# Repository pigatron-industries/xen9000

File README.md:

# XEN-9000
This project documents a completely DIY modular synthesizer build.

## Contents

* [Build Process](build_process.md)
* [Modules](modules/modules.md)

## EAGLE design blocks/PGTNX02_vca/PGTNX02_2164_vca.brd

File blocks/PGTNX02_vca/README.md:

# History

PGTNX02_2164

## V1
* Unlabelled
* C15 has wrong polarity.
* Linear/Exponential switch headers are mislabelled and inner ones are in the wrong order.
  SWLxx should be SWCxx. SWCxx should be SWExx. SWExx should be SWLxx.

Connections for Exponential mode:

```
  * *
    |
  * *
  |
  * *
```

Connections for Linear mode:

```
  * *--+
  |    |
  * *  |
       |
  * *--+
```

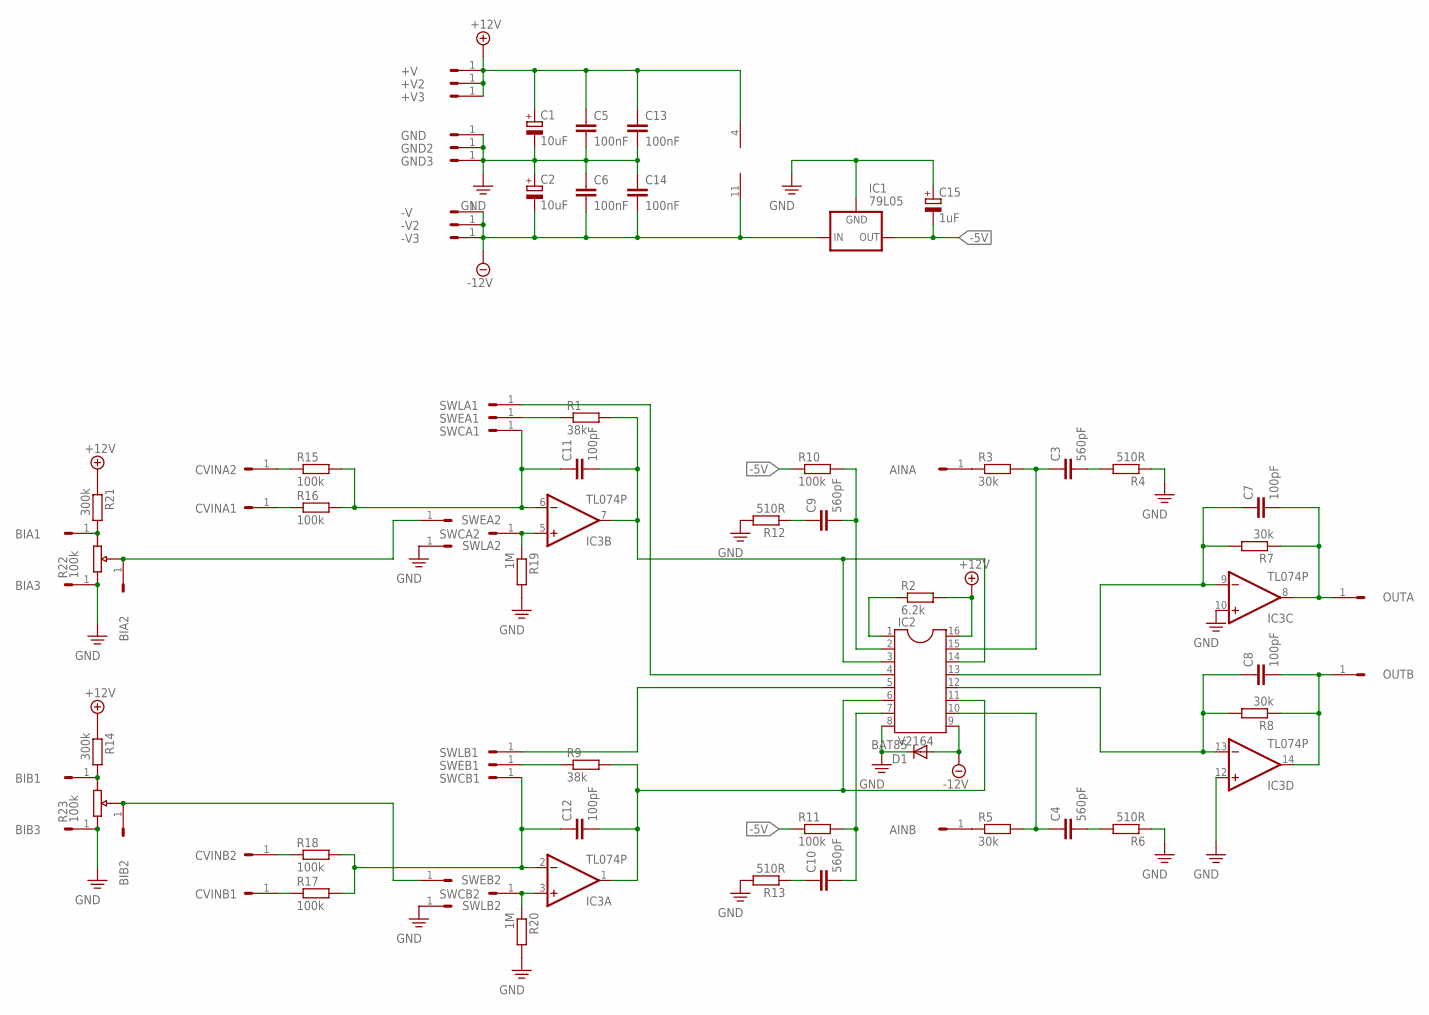
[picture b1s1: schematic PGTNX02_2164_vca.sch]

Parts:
+V, +V2, +V3: HEADER/MALE/01
-V, -V2, -V3: HEADER/MALE/01
AINA: HEADER/MALE/01
AINB: HEADER/MALE/01
BIA1, BIA2, BIA3: HEADER/MALE/01
BIB1, BIB2, BIB3: HEADER/MALE/01
C1, C2: 10uF; E2,5-6
C3, C4, C9, C10: 560pF; CERAMICDISC/5
C5, C6, C13, C14: 100nF; CERAMICDISC/5
C7, C8, C11, C12: 100pF; CERAMICDISC/5
C15: 1uF; E2,5-6
CVINA1, CVINA2: HEADER/MALE/01
CVINB1, CVINB2: HEADER/MALE/01
D1: BAT85; DO35-7
GND, GND2, GND3: HEADER/MALE/01
IC1: 79L05; 79LXX
IC2: V2164; DIL16
IC3: TL074P; DIL14
OUTA: HEADER/MALE/01
OUTB: HEADER/MALE/01
R1, R9: 38k; RESISTOR/7.5
R2: 6.2k; RESISTOR/7.5
R3, R5, R7, R8: 30k; RESISTOR/7.5
R4, R6, R12, R13: 510R; RESISTOR/7.5
R10, R11, R15, R16, R17, R18: 100k; RESISTOR/7.5
R14, R21: 300k; RESISTOR/7.5
R19, R20: 1M; RESISTOR/7.5
SWCA1, SWCA2: HEADER/MALE/01
SWCB1, SWCB2: HEADER/MALE/01
SWEA1, SWEA2: HEADER/MALE/01
SWEB1, SWEB2: HEADER/MALE/01
SWLA1, SWLA2: HEADER/MALE/01
SWLB1, SWLB2: HEADER/MALE/01

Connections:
+12V: +V.1, +V2.1, +V3.1, C1.+, C5.1, C13.1, IC2.16, IC3.4 (V+), R2.2, R14.1, R21.1
-5V: C15.-, IC1.OUT, R10.1, R11.1
-12V: -V.1, -V2.1, -V3.1, C2.-, C6.2, C14.2, D1.A, IC1.IN, IC2.9, IC3.11 (V-)
unnamed: C9.2, IC2.2, R10.2
unnamed: IC2.1, R2.1
unnamed: AINA.1, R3.1
unnamed: C3.1, IC2.15, R3.2
unnamed: C3.2, R4.2
unnamed: C7.1, IC2.13, IC3.9 (-IN), R7.2
unnamed: AINB.1, R5.1
unnamed: C4.1, IC2.10, R5.2
unnamed: C4.2, R6.2
unnamed: C8.1, IC2.12, IC3.13 (-IN), R8.2
unnamed: C10.2, IC2.7, R11.2
unnamed: C9.1, R12.1
unnamed: C8.2, IC3.14 (OUT), OUTB.1, R8.1
unnamed: C7.2, IC3.8 (OUT), OUTA.1, R7.1
unnamed: R1.1, SWEA1.1
unnamed: C11.1, IC3.6 (-IN), R15.2, R16.2, SWCA1.1
unnamed: C10.1, R13.1
unnamed: C12.2, IC2.6, IC2.11, IC3.1 (OUT), R9.2
unnamed: IC2.4, SWLA1.1
unnamed: C11.2, IC2.3, IC2.14, IC3.7 (OUT), R1.2
unnamed: BIB2.1, SWEB2.1
unnamed: CVINA2.1, R15.1
unnamed: CVINA1.1, R16.1
unnamed: CVINB1.1, R17.1
unnamed: CVINB2.1, R18.1
unnamed: C12.1, IC3.2 (-IN), R17.2, R18.2, SWCB1.1
unnamed: R9.1, SWEB1.1
unnamed: IC2.5, SWLB1.1
unnamed: IC3.5 (+IN), R19.1, SWCA2.1
unnamed: IC3.3 (+IN), R20.1, SWCB2.1
unnamed: BIA1.1, R21.2
unnamed: BIB1.1, R14.2
unnamed: BIA2.1, SWEA2.1
PE: BIA3.1, BIB3.1, C1.-, C2.+, C5.2, C6.1, C13.2, C14.1, C15.+, D1.C, GND.1, GND2.1, GND3.1, IC1.GND, IC2.8, IC3.10 (+IN), IC3.12 (+IN), R4.1, R6.1, R12.2, R13.2, R19.2, R20.2, SWLA2.1, SWLB2.1

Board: 2 copper layers, 80 parts (0 on the bottom side), 37 nets, no tracks yet.

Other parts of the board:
U$1, U$2, U$3, U$4: STANDOFF/3.0
U$5: PIGATRON-LOGO

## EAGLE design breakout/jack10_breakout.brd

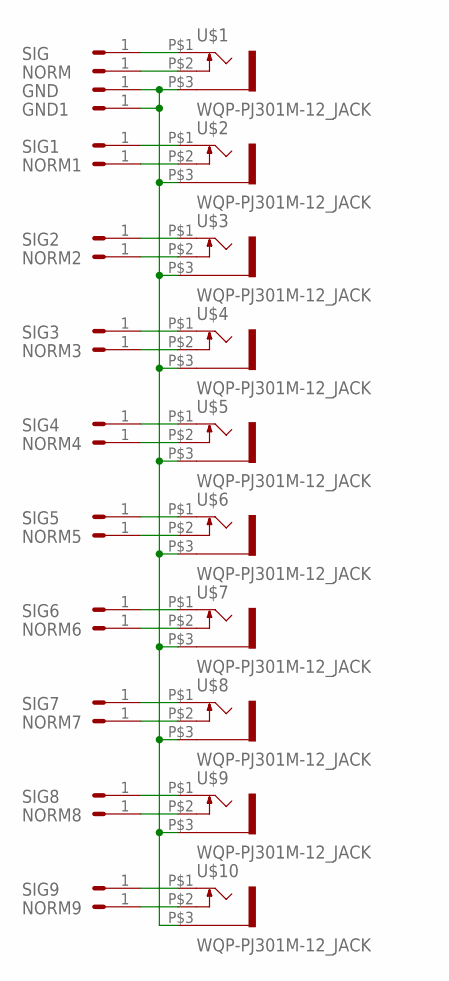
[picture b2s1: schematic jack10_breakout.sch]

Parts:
GND, GND1: HEADER/MALE/01
NORM, NORM1, NORM2, NORM3, NORM4, NORM5, NORM6, NORM7, NORM8, NORM9: HEADER/MALE/01
SIG, SIG1, SIG2, SIG3, SIG4, SIG5, SIG6, SIG7, SIG8, SIG9: HEADER/MALE/01
U$1, U$2, U$3, U$4, U$5, U$6, U$7, U$8, U$9, U$10: WQP-PJ301M-12_JACK

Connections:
unnamed: SIG.1, U$1.P$1 (2)
unnamed: NORM.1, U$1.P$2 (3)
unnamed: SIG1.1, U$2.P$1 (2)
unnamed: NORM1.1, U$2.P$2 (3)
unnamed: SIG2.1, U$3.P$1 (2)
unnamed: NORM2.1, U$3.P$2 (3)
unnamed: SIG3.1, U$4.P$1 (2)
unnamed: NORM3.1, U$4.P$2 (3)
unnamed: GND.1, GND1.1, U$1.P$3 (1), U$2.P$3 (1), U$3.P$3 (1), U$4.P$3 (1), U$5.P$3 (1), U$6.P$3 (1), U$7.P$3 (1), U$8.P$3 (1), U$9.P$3 (1), U$10.P$3 (1)
unnamed: SIG4.1, U$5.P$1 (2)
unnamed: NORM4.1, U$5.P$2 (3)
unnamed: SIG5.1, U$6.P$1 (2)
unnamed: NORM5.1, U$6.P$2 (3)
unnamed: SIG6.1, U$7.P$1 (2)
unnamed: NORM6.1, U$7.P$2 (3)
unnamed: SIG7.1, U$8.P$1 (2)
unnamed: NORM7.1, U$8.P$2 (3)
unnamed: SIG8.1, U$9.P$1 (2)
unnamed: NORM8.1, U$9.P$2 (3)
unnamed: SIG9.1, U$10.P$1 (2)
unnamed: NORM9.1, U$10.P$2 (3)

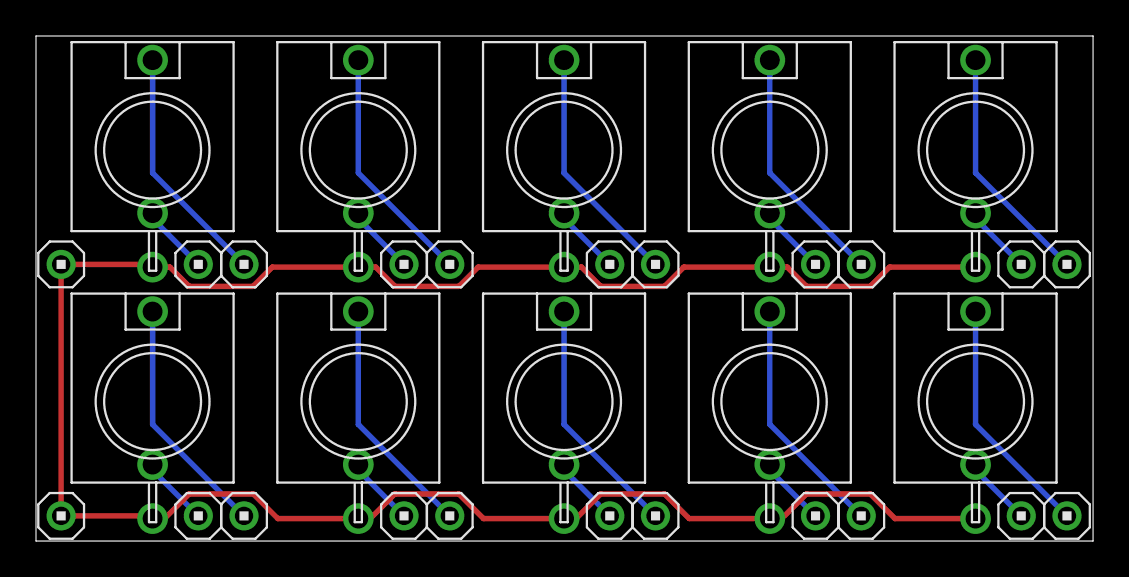
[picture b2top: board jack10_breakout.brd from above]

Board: 2 copper layers, 58.7 x 28.1 mm, 32 parts (0 on the bottom side), 21 nets.

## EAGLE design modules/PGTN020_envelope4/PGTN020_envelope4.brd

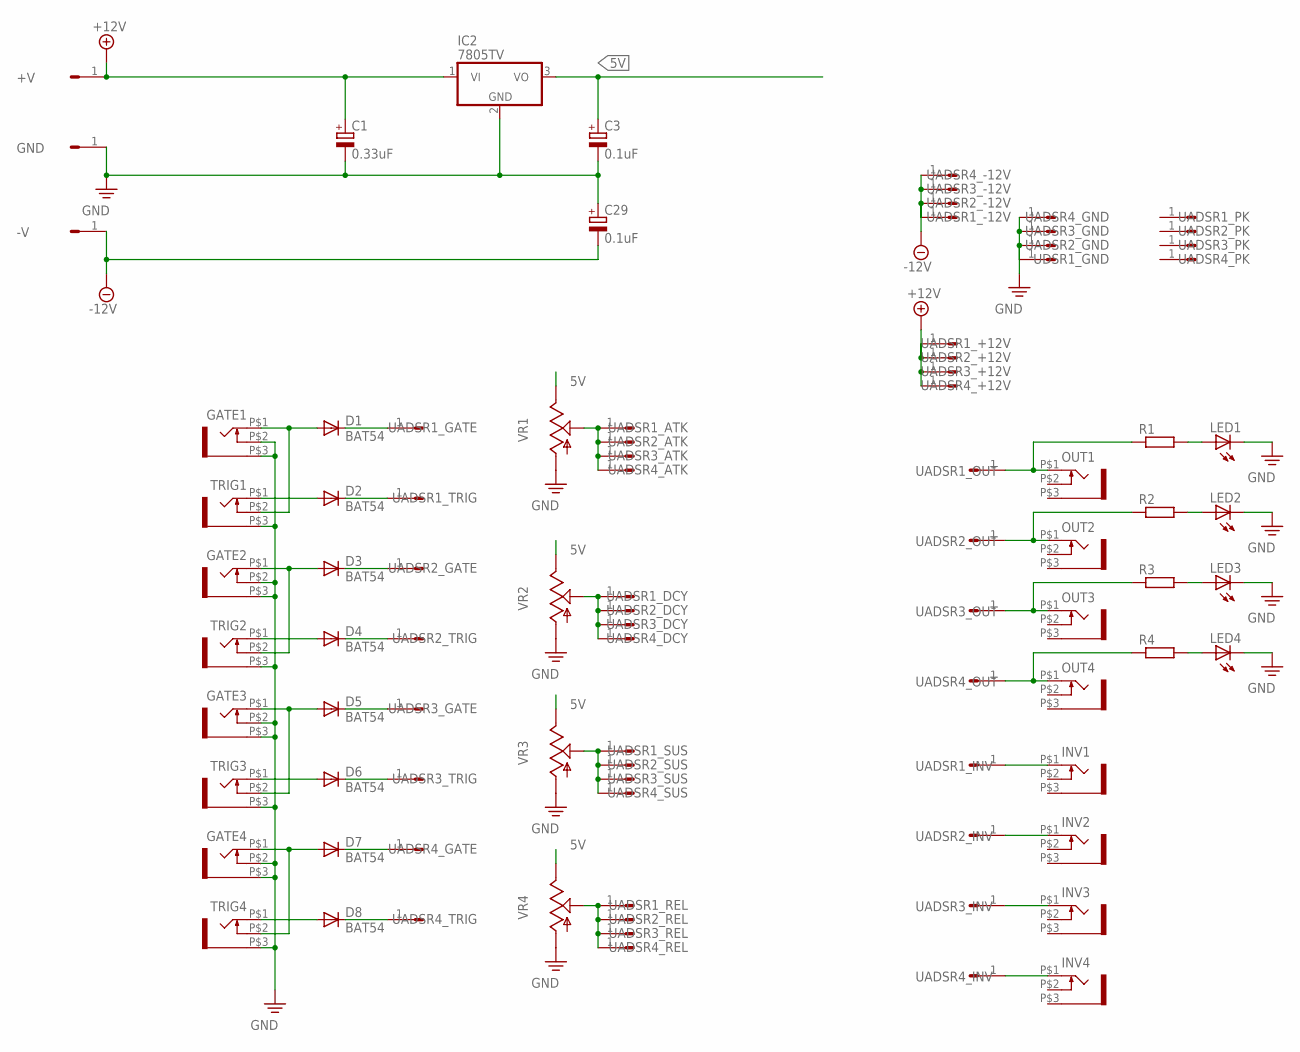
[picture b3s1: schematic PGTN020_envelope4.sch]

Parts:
+V: HEADER/MALE/01
-V: HEADER/MALE/01
C1: 0.33uF; E2,5-6
C3, C29: 0.1uF; E2,5-6
D1, D2, D3, D4, D5, D6, D7, D8: BAT54; DO35-7
GATE1, GATE2, GATE3, GATE4: WQP-PJ301M-12_JACK
GND: HEADER/MALE/01
IC2: 7805TV; TO220V
INV1, INV2, INV3, INV4: WQP-PJ301M-12_JACK
LED1, LED2, LED3, LED4: LED5MM
OUT1, OUT2, OUT3, OUT4: WQP-PJ301M-12_JACK
R1, R2, R3, R4: RESISTORRESISTOR/UPRIGHT/7.5; RESISTOR/7.5
TRIG1, TRIG2, TRIG3, TRIG4: WQP-PJ301M-12_JACK
UADSR1_+12V, UADSR1_-12V, UADSR1_ATK, UADSR1_DCY, UADSR1_GATE, UADSR1_INV, UADSR1_OUT, UADSR1_PK, UADSR1_REL, UADSR1_SUS, UADSR1_TRIG, UADSR2_+12V, UADSR2_-12V, UADSR2_ATK, UADSR2_DCY, UADSR2_GATE, UADSR2_GND, UADSR2_INV, UADSR2_OUT, UADSR2_PK, UADSR2_REL, UADSR2_SUS, UADSR2_TRIG, UADSR3_+12V, UADSR3_-12V, UADSR3_ATK, UADSR3_DCY, UADSR3_GATE, UADSR3_GND, UADSR3_INV, UADSR3_OUT, UADSR3_PK, UADSR3_REL, UADSR3_SUS, UADSR3_TRIG, UADSR4_+12V, UADSR4_-12V, UADSR4_ATK, UADSR4_DCY, UADSR4_GATE, UADSR4_GND, UADSR4_INV, UADSR4_OUT, UADSR4_PK, UADSR4_REL, UADSR4_SUS, UADSR4_TRIG: HEADER/MALE/01
UDSR1_GND: HEADER/MALE/01
VR1, VR2, VR3, VR4: 9MM_SNAP-IN_POT_; 9MM_SNAP-IN_POT

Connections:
5V: C3.+, IC2.3 (VO), VR1.3 (E), VR2.3 (E), VR3.3 (E), VR4.3 (E)
+12V: +V.1, C1.+, IC2.1 (VI), UADSR1_+12V.1, UADSR2_+12V.1, UADSR3_+12V.1, UADSR4_+12V.1
-12V: -V.1, C29.-, UADSR1_-12V.1, UADSR2_-12V.1, UADSR3_-12V.1, UADSR4_-12V.1
unnamed: OUT3.P$1 (2), R3.1, UADSR3_OUT.1
unnamed: OUT4.P$1 (2), R4.1, UADSR4_OUT.1
unnamed: INV1.P$1 (2), UADSR1_INV.1
unnamed: INV2.P$1 (2), UADSR2_INV.1
unnamed: INV3.P$1 (2), UADSR3_INV.1
unnamed: INV4.P$1 (2), UADSR4_INV.1
unnamed: D1.C, UADSR1_GATE.1
unnamed: D2.C, UADSR1_TRIG.1
unnamed: D1.A, GATE1.P$1 (2), TRIG1.P$2 (3)
unnamed: D2.A, TRIG1.P$1 (2)
unnamed: D3.A, GATE2.P$1 (2), TRIG2.P$2 (3)
unnamed: D4.A, TRIG2.P$1 (2)
unnamed: D5.A, GATE3.P$1 (2), TRIG3.P$2 (3)
unnamed: D6.A, TRIG3.P$1 (2)
unnamed: D7.A, GATE4.P$1 (2), TRIG4.P$2 (3)
unnamed: D8.A, TRIG4.P$1 (2)
unnamed: OUT1.P$1 (2), R1.1, UADSR1_OUT.1
unnamed: OUT2.P$1 (2), R2.1, UADSR2_OUT.1
unnamed: UADSR1_ATK.1, UADSR2_ATK.1, UADSR3_ATK.1, UADSR4_ATK.1, VR1.2 (S)
unnamed: UADSR1_DCY.1, UADSR2_DCY.1, UADSR3_DCY.1, UADSR4_DCY.1, VR2.2 (S)
unnamed: UADSR1_SUS.1, UADSR2_SUS.1, UADSR3_SUS.1, UADSR4_SUS.1, VR3.2 (S)
unnamed: UADSR1_REL.1, UADSR2_REL.1, UADSR3_REL.1, UADSR4_REL.1, VR4.2 (S)
unnamed: D3.C, UADSR2_GATE.1
unnamed: D4.C, UADSR2_TRIG.1
unnamed: D5.C, UADSR3_GATE.1
unnamed: D6.C, UADSR3_TRIG.1
unnamed: D7.C, UADSR4_GATE.1
unnamed: D8.C, UADSR4_TRIG.1
unnamed: LED1.A, R1.2
unnamed: LED2.A, R2.2
unnamed: LED3.A, R3.2
unnamed: LED4.A, R4.2
PE: C1.-, C3.-, C29.+, GATE1.P$2 (3), GATE1.P$3 (1), GATE2.P$2 (3), GATE2.P$3 (1), GATE3.P$2 (3), GATE3.P$3 (1), GATE4.P$2 (3), GATE4.P$3 (1), GND.1, IC2.2 (GND), LED1.K (C), LED2.K (C), LED3.K (C), LED4.K (C), TRIG1.P$3 (1), TRIG2.P$3 (1), TRIG3.P$3 (1), TRIG4.P$3 (1), UADSR2_GND.1, UADSR3_GND.1, UADSR4_GND.1, UDSR1_GND.1, VR1.1 (A), VR2.1 (A), VR3.1 (A), VR4.1 (A)

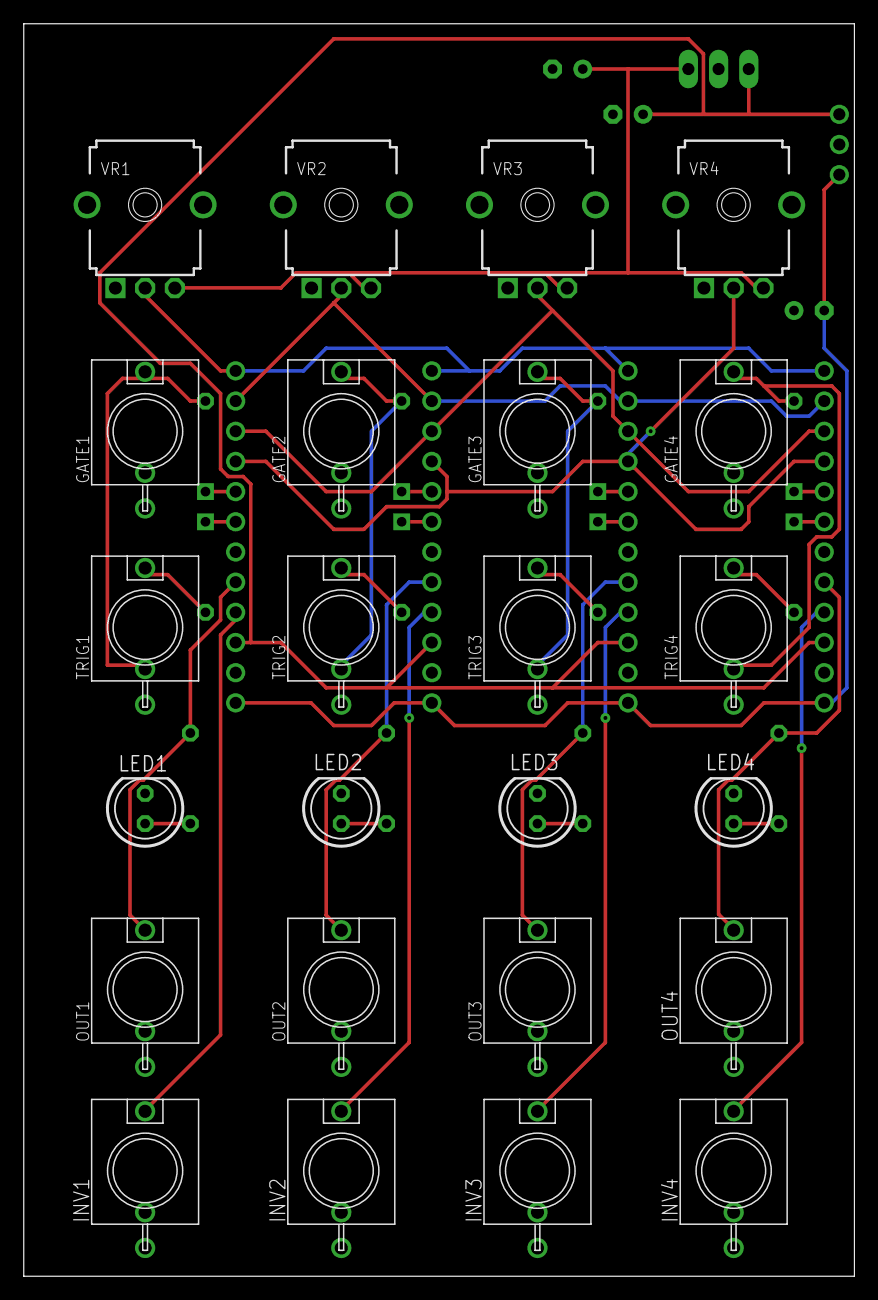
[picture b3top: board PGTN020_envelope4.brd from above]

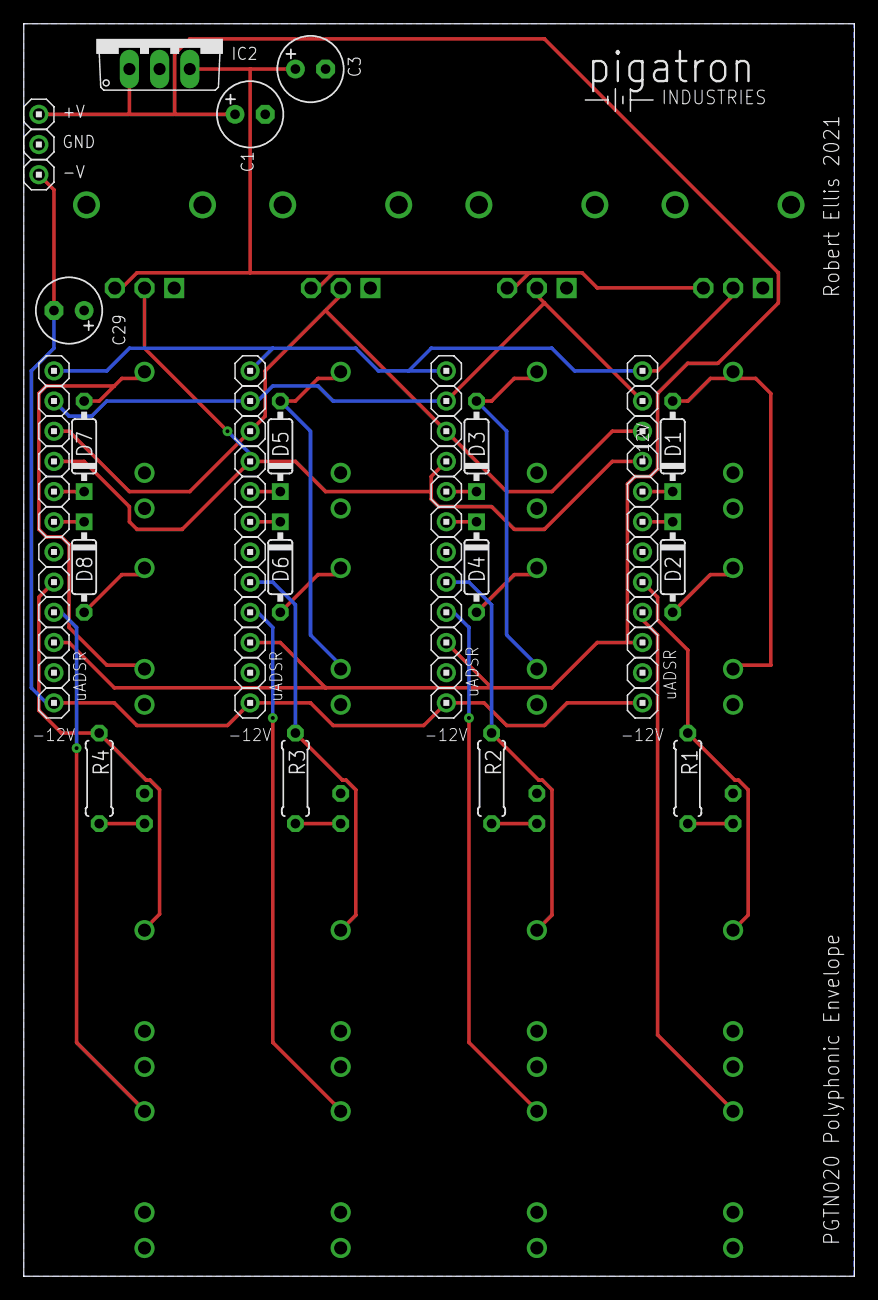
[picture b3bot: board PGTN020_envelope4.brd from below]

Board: 2 copper layers, 69.9 x 105.4 mm, 92 parts (68 on the bottom side), 36 nets.

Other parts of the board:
U$5: PIGATRON-LOGO

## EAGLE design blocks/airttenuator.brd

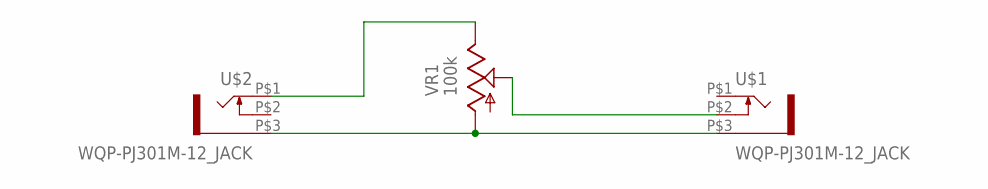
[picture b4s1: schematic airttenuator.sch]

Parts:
U$1, U$2: WQP-PJ301M-12_JACK
VR1: 100k; 9MM_SNAP-IN_POT

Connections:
unnamed: U$1.P$3 (1), U$2.P$3 (1), VR1.1 (A)
unnamed: U$2.P$1 (2), VR1.3 (E)
unnamed: U$1.P$2 (3), VR1.2 (S)

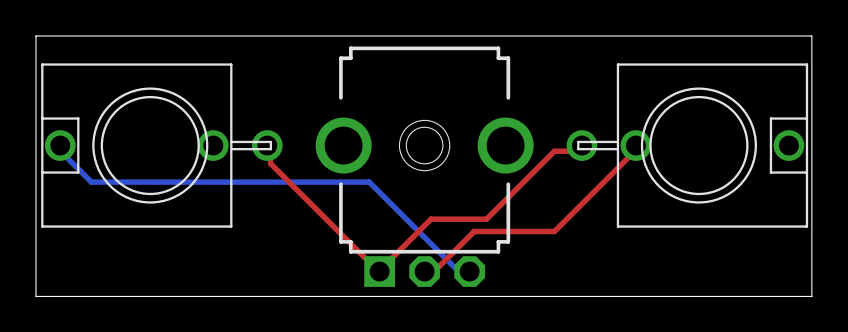
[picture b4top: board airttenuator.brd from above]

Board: 2 copper layers, 43.1 x 14.5 mm, 4 parts (1 on the bottom side), 3 nets.

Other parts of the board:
U$3: PIGATRON-LOGO

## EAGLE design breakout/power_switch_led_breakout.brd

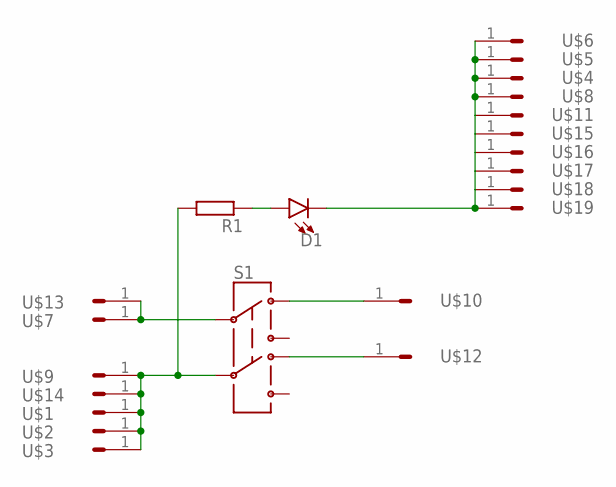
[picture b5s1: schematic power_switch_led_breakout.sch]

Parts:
D1: LED5MM; LED_5MM
R1: RESISTORRESISTOR/UPRIGHT/7.5; RESISTOR/7.5
S1: SWITCH-DPDTPTH1; SWITCH-DPDT_SUBMINIATURE
U$1, U$2, U$3, U$4, U$5, U$6, U$7, U$8, U$9, U$10, U$11, U$12, U$13, U$14, U$15, U$16, U$17, U$18, U$19: HEADER/MALE/01NOBORDER; HEADER/MALE/01/NOBORDER

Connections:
unnamed: S1.2, U$7.1, U$13.1
unnamed: S1.1, U$10.1
unnamed: D1.A, R1.1
unnamed: S1.4, U$12.1
unnamed: D1.K (C), U$4.1, U$5.1, U$6.1, U$8.1, U$11.1, U$15.1, U$16.1, U$17.1, U$18.1, U$19.1
unnamed: R1.2, S1.5, U$1.1, U$2.1, U$3.1, U$9.1, U$14.1

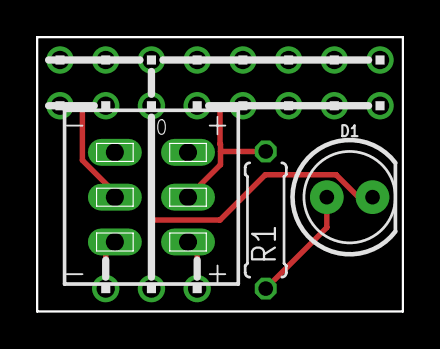
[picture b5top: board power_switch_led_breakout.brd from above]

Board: 2 copper layers, 20.3 x 15.2 mm, 22 parts (0 on the bottom side), 6 nets.

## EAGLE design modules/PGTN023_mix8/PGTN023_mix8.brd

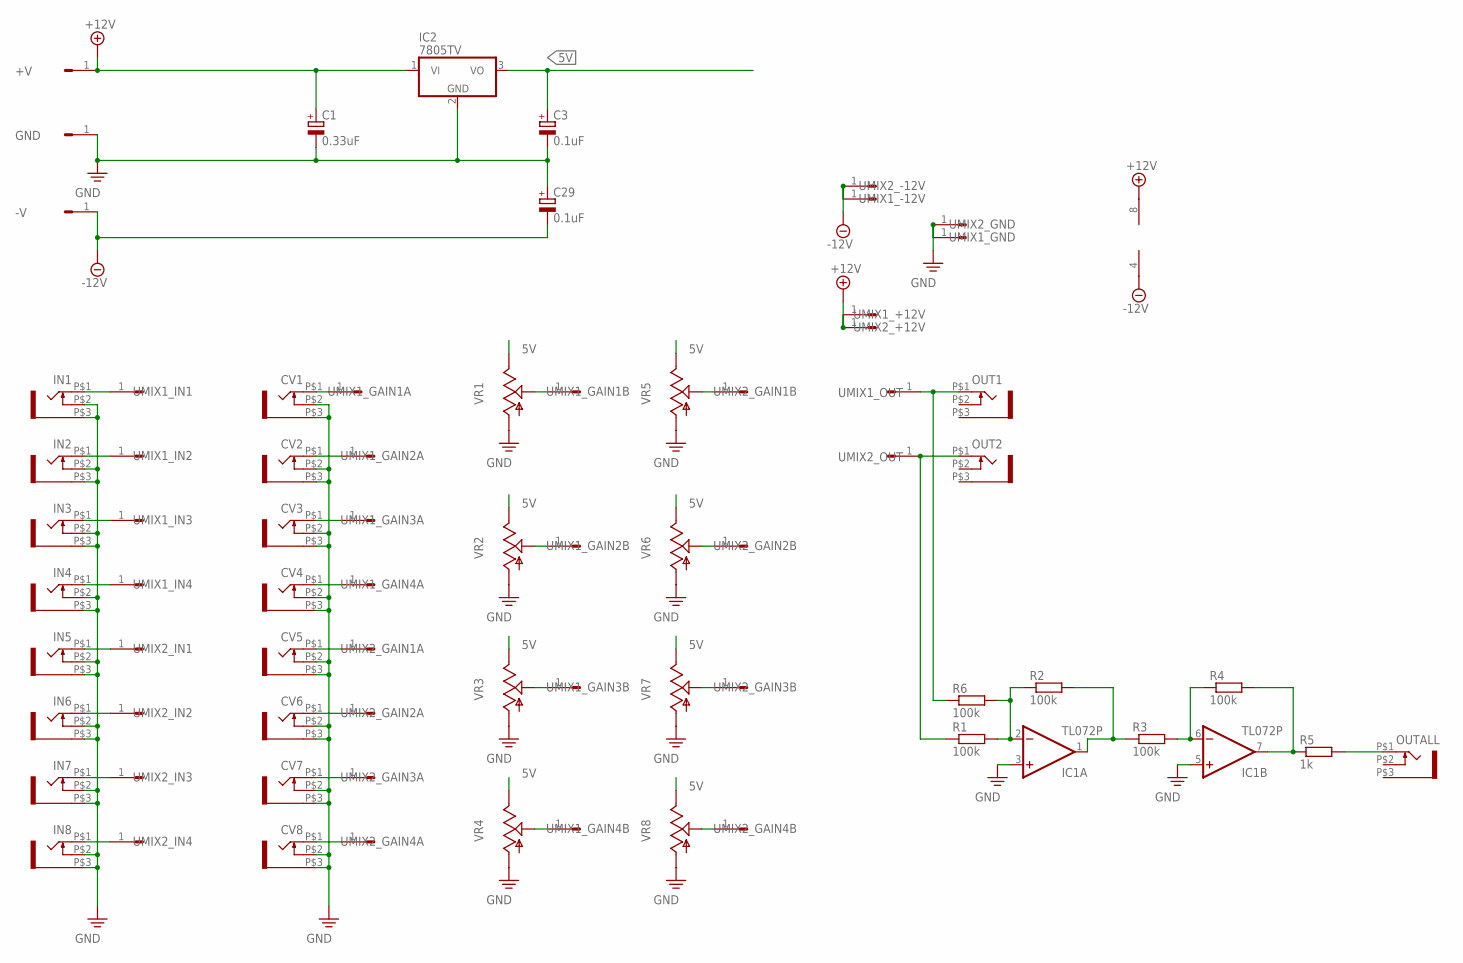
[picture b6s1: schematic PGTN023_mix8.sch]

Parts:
+V: HEADER/MALE/01
-V: HEADER/MALE/01
C1: 0.33uF; E2,5-6
C3, C29: 0.1uF; E2,5-6
CV1, CV2, CV3, CV4, CV5, CV6, CV7, CV8: WQP-PJ301M-12_JACK
GND: HEADER/MALE/01
IC1: TL072P; DIL08
IC2: 7805TV; TO220V
IN1, IN2, IN3, IN4, IN5, IN6, IN7, IN8: WQP-PJ301M-12_JACK
OUT1, OUT2: WQP-PJ301M-12_JACK
OUTALL: WQP-PJ301M-12_JACK
R1, R2, R3, R4, R6: 100k; RESISTOR/7.5
R5: 1k; RESISTOR/7.5
UMIX1_+12V, UMIX1_-12V, UMIX1_GAIN1A, UMIX1_GAIN1B, UMIX1_GAIN2A, UMIX1_GAIN2B, UMIX1_GAIN3A, UMIX1_GAIN3B, UMIX1_GAIN4A, UMIX1_GAIN4B, UMIX1_GND, UMIX1_IN1, UMIX1_IN2, UMIX1_IN3, UMIX1_IN4, UMIX1_OUT, UMIX2_+12V, UMIX2_-12V, UMIX2_GAIN1A, UMIX2_GAIN1B, UMIX2_GAIN2A, UMIX2_GAIN2B, UMIX2_GAIN3A, UMIX2_GAIN3B, UMIX2_GAIN4A, UMIX2_GAIN4B, UMIX2_GND, UMIX2_IN1, UMIX2_IN2, UMIX2_IN3, UMIX2_IN4, UMIX2_OUT: HEADER/MALE/01
VR1, VR2, VR3, VR4, VR5, VR6, VR7, VR8: 9MM_SNAP-IN_POT_; 9MM_SNAP-IN_POT

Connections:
5V: C3.+, IC2.3 (VO), VR1.3 (E), VR2.3 (E), VR3.3 (E), VR4.3 (E), VR5.3 (E), VR6.3 (E), VR7.3 (E), VR8.3 (E)
+12V: +V.1, C1.+, IC1.8 (V+), IC2.1 (VI), UMIX1_+12V.1, UMIX2_+12V.1
-12V: -V.1, C29.-, IC1.4 (V-), UMIX1_-12V.1, UMIX2_-12V.1
unnamed: IN1.P$1 (2), UMIX1_IN1.1
unnamed: IN2.P$1 (2), UMIX1_IN2.1
unnamed: IN3.P$1 (2), UMIX1_IN3.1
unnamed: IN4.P$1 (2), UMIX1_IN4.1
unnamed: IN5.P$1 (2), UMIX2_IN1.1
unnamed: IN6.P$1 (2), UMIX2_IN2.1
unnamed: IN7.P$1 (2), UMIX2_IN3.1
unnamed: IN8.P$1 (2), UMIX2_IN4.1
unnamed: CV1.P$1 (2), UMIX1_GAIN1A.1
unnamed: CV2.P$1 (2), UMIX1_GAIN2A.1
unnamed: CV3.P$1 (2), UMIX1_GAIN3A.1
unnamed: CV4.P$1 (2), UMIX1_GAIN4A.1
unnamed: CV5.P$1 (2), UMIX2_GAIN1A.1
unnamed: CV6.P$1 (2), UMIX2_GAIN2A.1
unnamed: CV7.P$1 (2), UMIX2_GAIN3A.1
unnamed: CV8.P$1 (2), UMIX2_GAIN4A.1
unnamed: OUT1.P$1 (2), R6.1, UMIX1_OUT.1
unnamed: OUT2.P$1 (2), R1.1, UMIX2_OUT.1
unnamed: UMIX1_GAIN1B.1, VR1.2 (S)
unnamed: UMIX1_GAIN2B.1, VR2.2 (S)
unnamed: UMIX1_GAIN3B.1, VR3.2 (S)
unnamed: UMIX1_GAIN4B.1, VR4.2 (S)
unnamed: UMIX2_GAIN1B.1, VR5.2 (S)
unnamed: UMIX2_GAIN2B.1, VR6.2 (S)
unnamed: UMIX2_GAIN3B.1, VR7.2 (S)
unnamed: UMIX2_GAIN4B.1, VR8.2 (S)
unnamed: IC1.2 (-IN), R1.2, R2.1, R6.2
unnamed: IC1.1 (OUT), R2.2, R3.1
unnamed: IC1.6 (-IN), R3.2, R4.1
unnamed: IC1.7 (OUT), R4.2, R5.1
unnamed: OUTALL.P$1 (2), R5.2
PE: C1.-, C3.-, C29.+, CV1.P$2 (3), CV1.P$3 (1), CV2.P$2 (3), CV2.P$3 (1), CV3.P$2 (3), CV3.P$3 (1), CV4.P$2 (3), CV4.P$3 (1), CV5.P$2 (3), CV5.P$3 (1), CV6.P$2 (3), CV6.P$3 (1), CV7.P$2 (3), CV7.P$3 (1), CV8.P$2 (3), CV8.P$3 (1), GND.1, IC1.3 (+IN), IC1.5 (+IN), IC2.2 (GND), IN1.P$2 (3), IN1.P$3 (1), IN2.P$2 (3), IN2.P$3 (1), IN3.P$2 (3), IN3.P$3 (1), IN4.P$2 (3), IN4.P$3 (1), IN5.P$2 (3), IN5.P$3 (1), IN6.P$2 (3), IN6.P$3 (1), IN7.P$2 (3), IN7.P$3 (1), IN8.P$2 (3), IN8.P$3 (1), UMIX1_GND.1, UMIX2_GND.1, VR1.1 (A), VR2.1 (A), VR3.1 (A), VR4.1 (A), VR5.1 (A), VR6.1 (A), VR7.1 (A), VR8.1 (A)

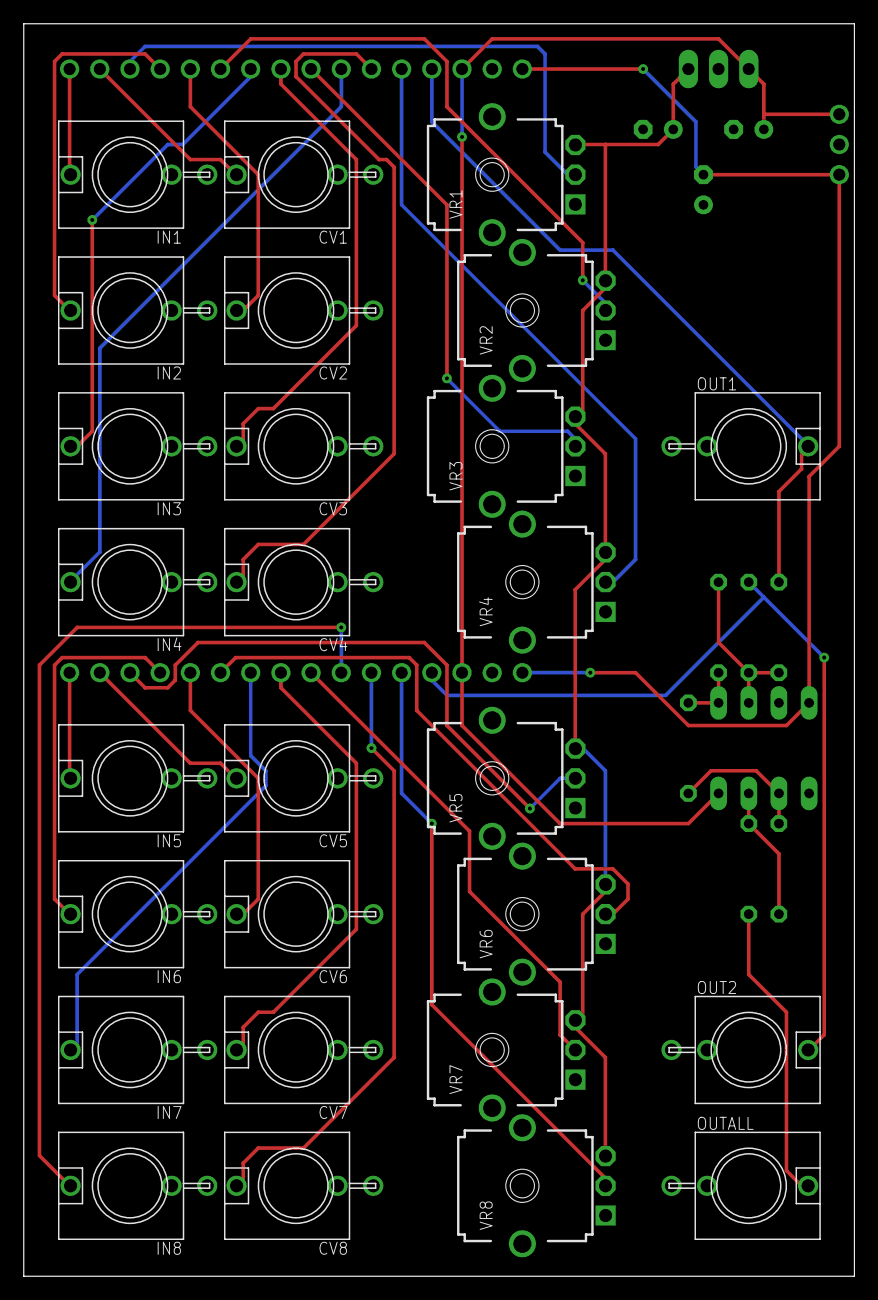
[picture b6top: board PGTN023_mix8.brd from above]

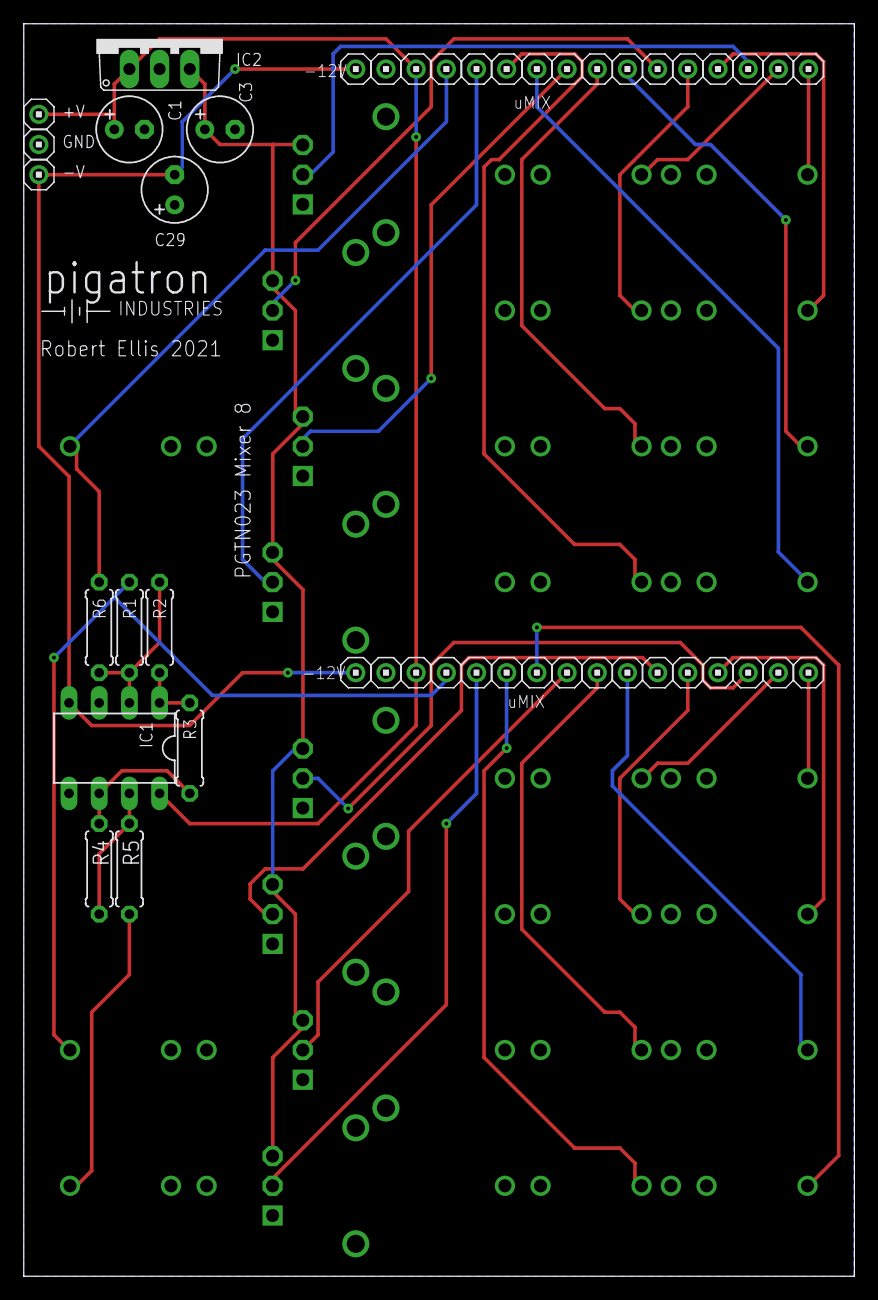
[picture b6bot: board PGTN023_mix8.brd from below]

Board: 2 copper layers, 69.9 x 105.4 mm, 74 parts (47 on the bottom side), 35 nets.

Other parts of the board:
U$5: PIGATRON-LOGO

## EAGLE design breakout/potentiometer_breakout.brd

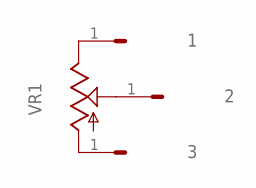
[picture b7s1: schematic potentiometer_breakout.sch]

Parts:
1, 2, 3: HEADER/MALE/01
VR1: 9MM_SNAP-IN_POT_; 9MM_SNAP-IN_POT

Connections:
unnamed: 1.1, VR1.3 (E)
unnamed: 2.1, VR1.2 (S)
unnamed: 3.1, VR1.1 (A)

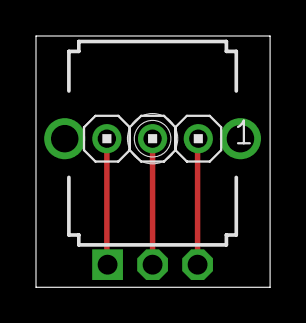
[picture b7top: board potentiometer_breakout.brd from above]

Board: 2 copper layers, 13.0 x 14.0 mm, 4 parts (0 on the bottom side), 3 nets.

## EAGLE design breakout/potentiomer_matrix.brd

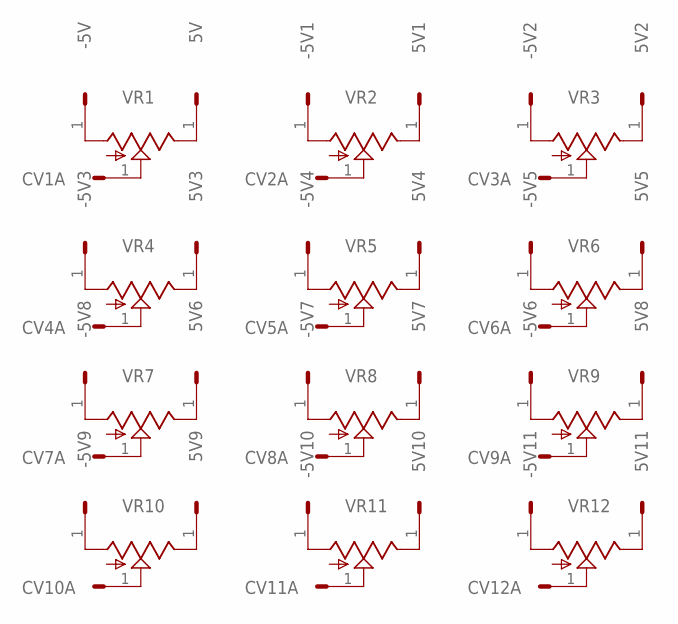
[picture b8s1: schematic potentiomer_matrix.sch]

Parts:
5V, 5V1, 5V2, 5V3, 5V4, 5V5, 5V6, 5V7, 5V8, 5V9, 5V10, 5V11: HEADER/MALE/01
-5V, -5V1, -5V2, -5V3, -5V4, -5V5, -5V6, -5V7, -5V8, -5V9, -5V10, -5V11: HEADER/MALE/01
CV1A, CV2A, CV3A, CV4A, CV5A, CV6A, CV7A, CV8A, CV9A, CV10A, CV11A, CV12A: HEADER/MALE/01
VR1, VR2, VR3, VR4, VR5, VR6, VR7, VR8, VR9, VR10, VR11, VR12: 9MM_SNAP-IN_POT_; 9MM_SNAP-IN_POT

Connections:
unnamed: 5V.1, VR1.3 (E)
unnamed: 5V1.1, VR2.3 (E)
unnamed: 5V2.1, VR3.3 (E)
unnamed: 5V3.1, VR4.3 (E)
unnamed: 5V4.1, VR5.3 (E)
unnamed: 5V5.1, VR6.3 (E)
unnamed: 5V6.1, VR7.3 (E)
unnamed: 5V7.1, VR8.3 (E)
unnamed: CV1A.1, VR1.2 (S)
unnamed: 5V8.1, VR9.3 (E)
unnamed: CV2A.1, VR2.2 (S)
unnamed: 5V9.1, VR10.3 (E)
unnamed: CV3A.1, VR3.2 (S)
unnamed: 5V10.1, VR11.3 (E)
unnamed: CV4A.1, VR4.2 (S)
unnamed: 5V11.1, VR12.3 (E)
unnamed: CV5A.1, VR5.2 (S)
unnamed: -5V1.1, VR2.1 (A)
unnamed: CV6A.1, VR6.2 (S)
unnamed: -5V2.1, VR3.1 (A)
unnamed: CV7A.1, VR7.2 (S)
unnamed: -5V3.1, VR4.1 (A)
unnamed: CV8A.1, VR8.2 (S)
unnamed: -5V4.1, VR5.1 (A)
unnamed: CV9A.1, VR9.2 (S)
unnamed: -5V5.1, VR6.1 (A)
unnamed: CV10A.1, VR10.2 (S)
unnamed: -5V6.1, VR9.1 (A)
unnamed: CV11A.1, VR11.2 (S)
unnamed: -5V.1, VR1.1 (A)
unnamed: CV12A.1, VR12.2 (S)
unnamed: -5V7.1, VR8.1 (A)
unnamed: -5V8.1, VR7.1 (A)
unnamed: -5V9.1, VR10.1 (A)
unnamed: -5V10.1, VR11.1 (A)
unnamed: -5V11.1, VR12.1 (A)

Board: 2 copper layers, 48 parts (0 on the bottom side), 36 nets, no tracks yet.

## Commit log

2018-11-04 build process
2018-11-04 modules list initial commit
2018-11-04 changed headers
2018-11-04 Added table of modules
2018-12-16 Added module codes
2019-01-06 Added percussive synth schematic
2019-01-28 Libraries
2019-02-13 Added files
2019-02-23 Correct file - was engraving not holes
2019-04-14 added sequencer
2019-05-11 Fix for following issues * Pin 12 of IC5 shorted to pin 10. Pin 12 should be GND, but not pin 10 so have to kludge on IC pin. * SHL_SWP3 should connect to GND. No big deal as can just connect pot dir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
2019-07-07 PGTN015 V2 - Fix pins 12 and 13 of IC3 (Op amp inputs) wrong way around.
2019-09-12 Added low pass/band pass filter block
2019-09-12 PGTN020 - ADSR Envelope with VCA
2019-12-29 Teensy board initial commit
2020-01-05 Committed a load of changes
2020-01-05 Modified boards to fit together better
2020-03-02 Added output resistors and xener voltage limiters.
2020-03-02 Add gcode files to .gitignore
2020-03-02 Blue Shift panel
2020-03-02 Octasource panel
2020-03-27 new design pcbs for midi2cv
2020-03-29 Update PGTNX05_mainboard.brd
    Tidied up dimensiosn docu, added extra mounting hole
2020-03-29 Added pigatron logo on solder mask layer
2020-04-15 Corrected resistor value
2020-04-17 Changed resistor value
2020-04-18 Added correct diode type BZX55C12
2020-04-24 Connected C7 to ground
2020-04-27 Added schematic for V2164 VCA + panels
2020-05-02 2164 vca board layout + rotary encoder breakout pcb
2020-05-16 Added error history to VCA, corrected some label errors and changed a resistor value.
2020-05-25 Changed 1M input resistors to 300k in filter to increase gain.
2020-06-20 Added breakout board designs + daisy eurorack motherboard
2020-06-21 Corrected Polarity of C15

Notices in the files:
parts and their libraries:
SparkFun-LED: Licensing: Creative Commons ShareAlike 4.0 International - https://creativecommons.org/licenses/by-sa/4.0
